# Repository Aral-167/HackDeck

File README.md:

# HackDeck
HackDeck is a simple Python-based utility designed to streamline the process of opening files, applications, URLs, and more from a single command interface. Whether you're a developer, power user, or just want to speed up your workflow, HackDeck makes it quick and intuitive to access the things you need. (My first PCB project so it's probably not even near good but I'm still trying.)

## Features
Open files, folders, or applications with simple commands.
Launch URLs in your default browser.
Customizable: add your own shortcuts and commands.
Cross-platform support (Windows, macOS, Linux).
Lightweight and easy to use.

## Bill of Materials
1. 9x Cherry MX Switches
2. 1x XIAO RP2040
3. 1x Case (2 3D printed parts)
4. 1x SK6812 MINI Leds
5. 9x Blank DSA Keycaps
6. 4x M3x16 Bolt
7. 4x M3 Heatset

## PCB

## Case

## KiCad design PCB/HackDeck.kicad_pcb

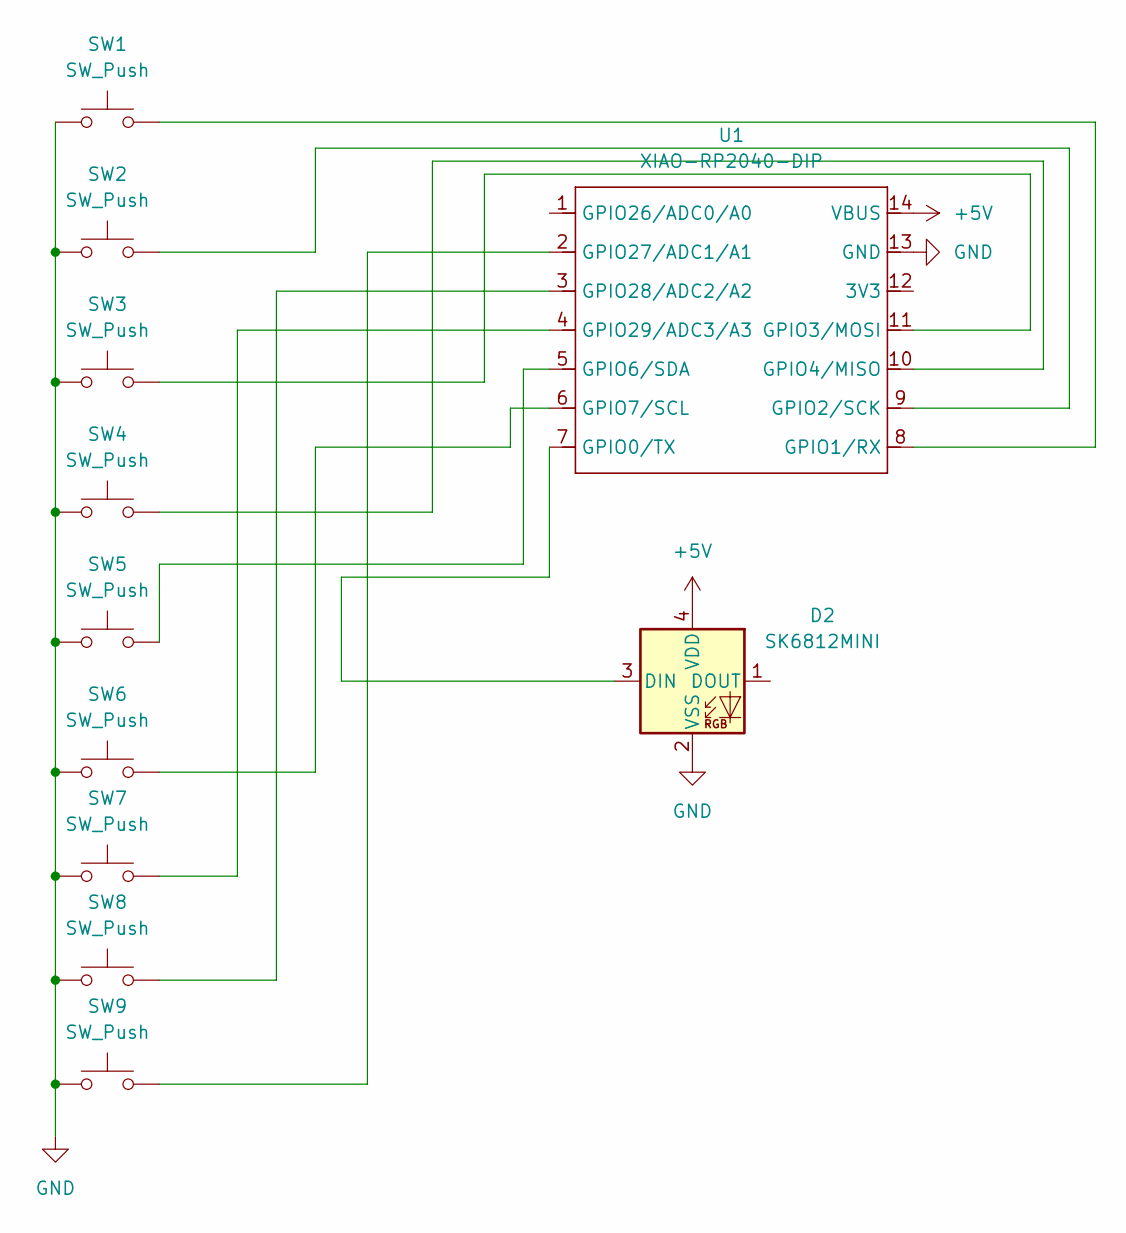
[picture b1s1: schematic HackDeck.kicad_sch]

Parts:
D2: SK6812MINI; LED_SK6812MINI_PLCC4_3.5x3.5mm_P1.75mm
SW1, SW2, SW3, SW4, SW5, SW6, SW7, SW8, SW9: SW_Push; SW_Cherry_MX_1.00u_PCB
U1: XIAO-RP2040-DIP

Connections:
+5V: D2.4 (VDD), U1.14 (VBUS)
GND: D2.2 (VSS), SW1.1, SW2.1, SW3.1, SW4.1, SW5.1, SW6.1, SW7.1, SW8.1, SW9.1, U1.13 (GND)
unnamed: D2.3 (DIN), U1.7 (GPIO0/TX)
unnamed: SW1.2, U1.8 (GPIO1/RX)
unnamed: SW2.2, U1.9 (GPIO2/SCK)
unnamed: SW3.2, U1.11 (GPIO3/MOSI)
unnamed: SW4.2, U1.10 (GPIO4/MISO)
unnamed: SW5.2, U1.5 (GPIO6/SDA)
unnamed: SW6.2, U1.6 (GPIO7/SCL)
unnamed: SW9.2, U1.2 (GPIO27/ADC1/A1)
unnamed: SW8.2, U1.3 (GPIO28/ADC2/A2)
unnamed: SW7.2, U1.4 (GPIO29/ADC3/A3)

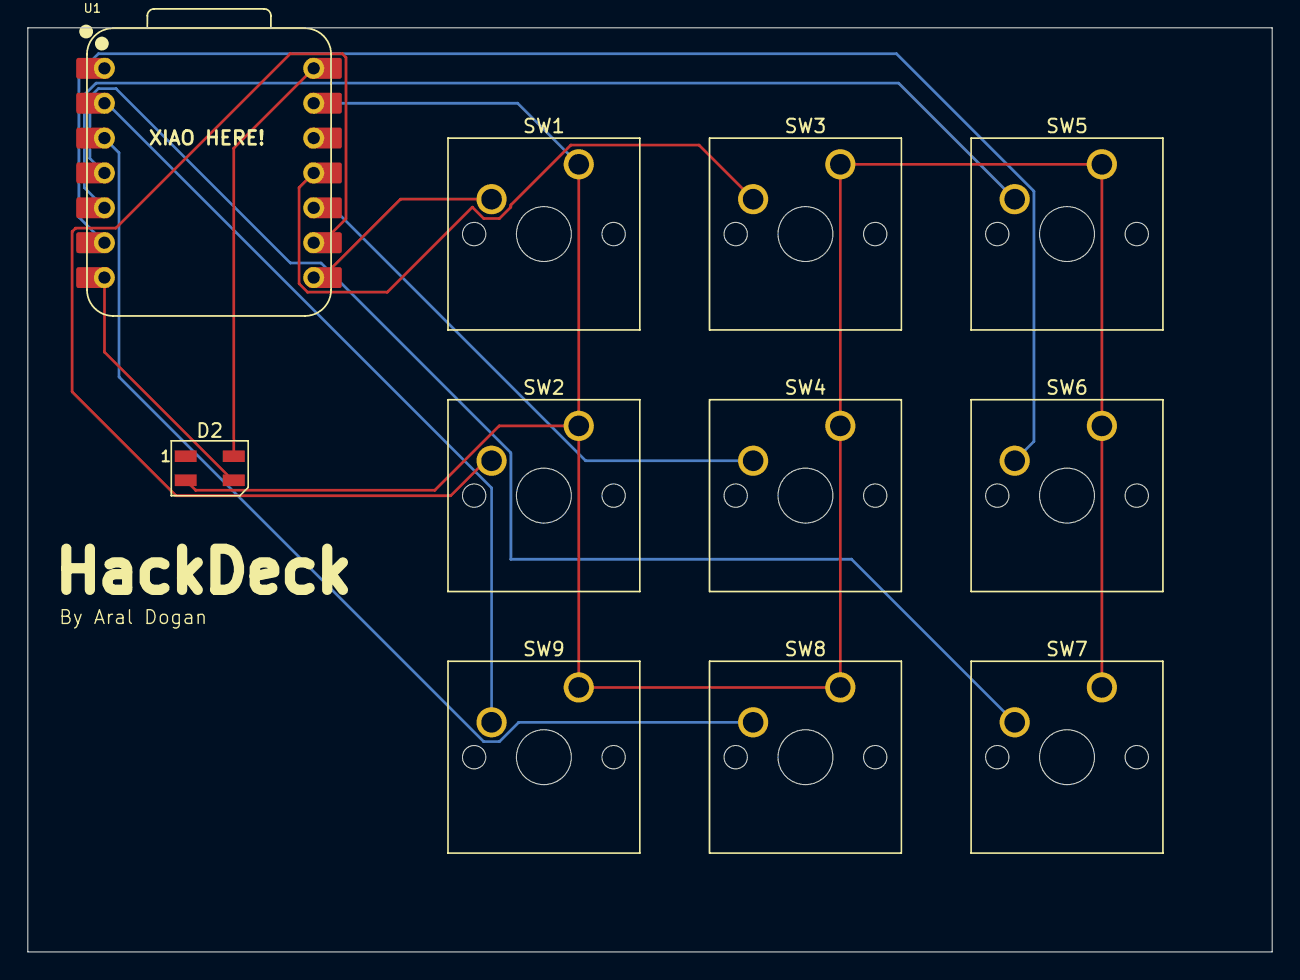
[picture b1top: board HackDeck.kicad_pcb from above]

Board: 2 copper layers, 90.6 x 67.3 mm, 11 parts (0 on the bottom side), 12 nets.

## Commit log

2025-07-15 main.py added
2025-07-15 added ctrl+t
2025-07-15 removed ctrl+t
2025-07-15 added chatgpt
2025-07-15 files added
2025-07-15 gerbers added
2025-07-15 added top
2025-07-15 added things to production
2025-07-15 images added
2025-08-15 main.py updated
2025-08-15 used delay
